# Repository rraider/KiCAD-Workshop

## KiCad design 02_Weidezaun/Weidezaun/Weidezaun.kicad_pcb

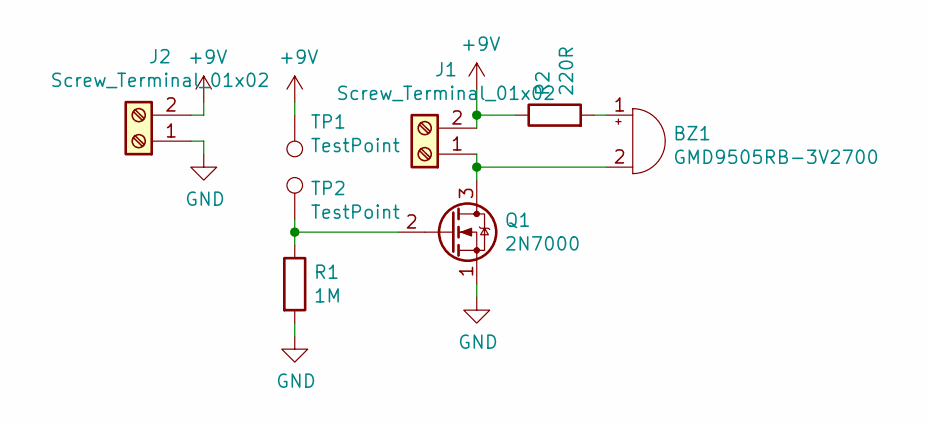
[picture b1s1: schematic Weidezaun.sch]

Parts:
BZ1: GMD9505RB-3V2700; Buzzer_TDK_PS1240P02BT_D12.2mm_H6.5mm
J1, J2: Screw_Terminal_01x02; TerminalBlock_bornier-2_P5.08mm
Q1: 2N7000; TO-92_Inline_Wide
R1: 1M; R_Axial_DIN0204_L3.6mm_D1.6mm_P7.62mm_Horizontal
R2: 220R; R_Axial_DIN0204_L3.6mm_D1.6mm_P7.62mm_Horizontal
TP1, TP2: TestPoint; testpoint_15x15

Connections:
+9V: J1.2, J2.2, R2.1, TP1.1
GND: J2.1, Q1.1 (S), R1.2
unnamed: BZ1.1 (-), R2.2
unnamed: BZ1.2 (+), J1.1, Q1.3 (D)
unnamed: Q1.2 (G), R1.1, TP2.1

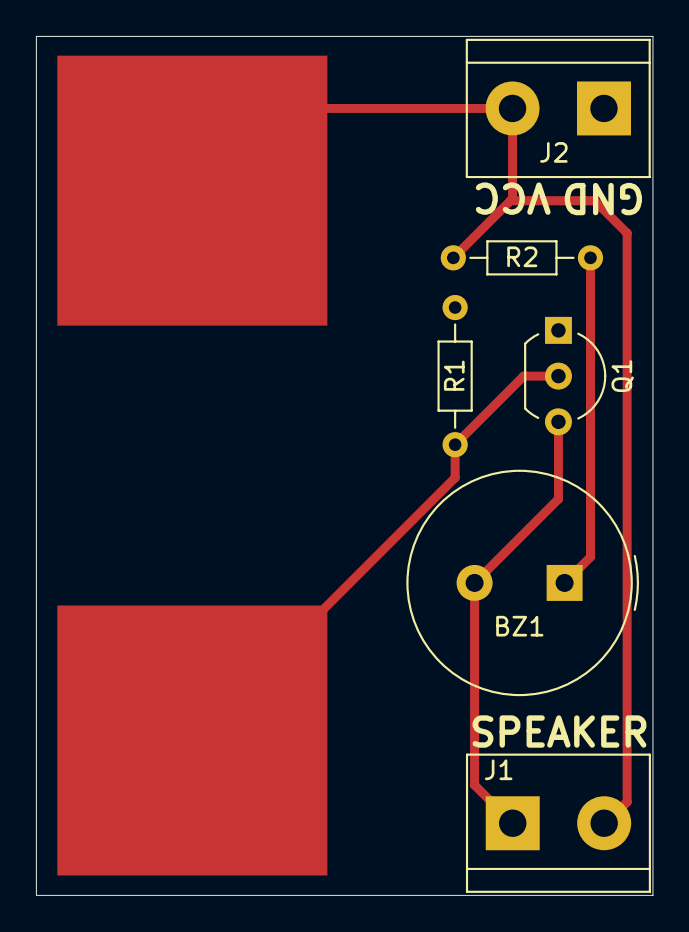
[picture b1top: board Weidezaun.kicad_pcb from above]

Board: 2 copper layers, 34.3 x 47.7 mm, 8 parts (0 on the bottom side), 5 nets.

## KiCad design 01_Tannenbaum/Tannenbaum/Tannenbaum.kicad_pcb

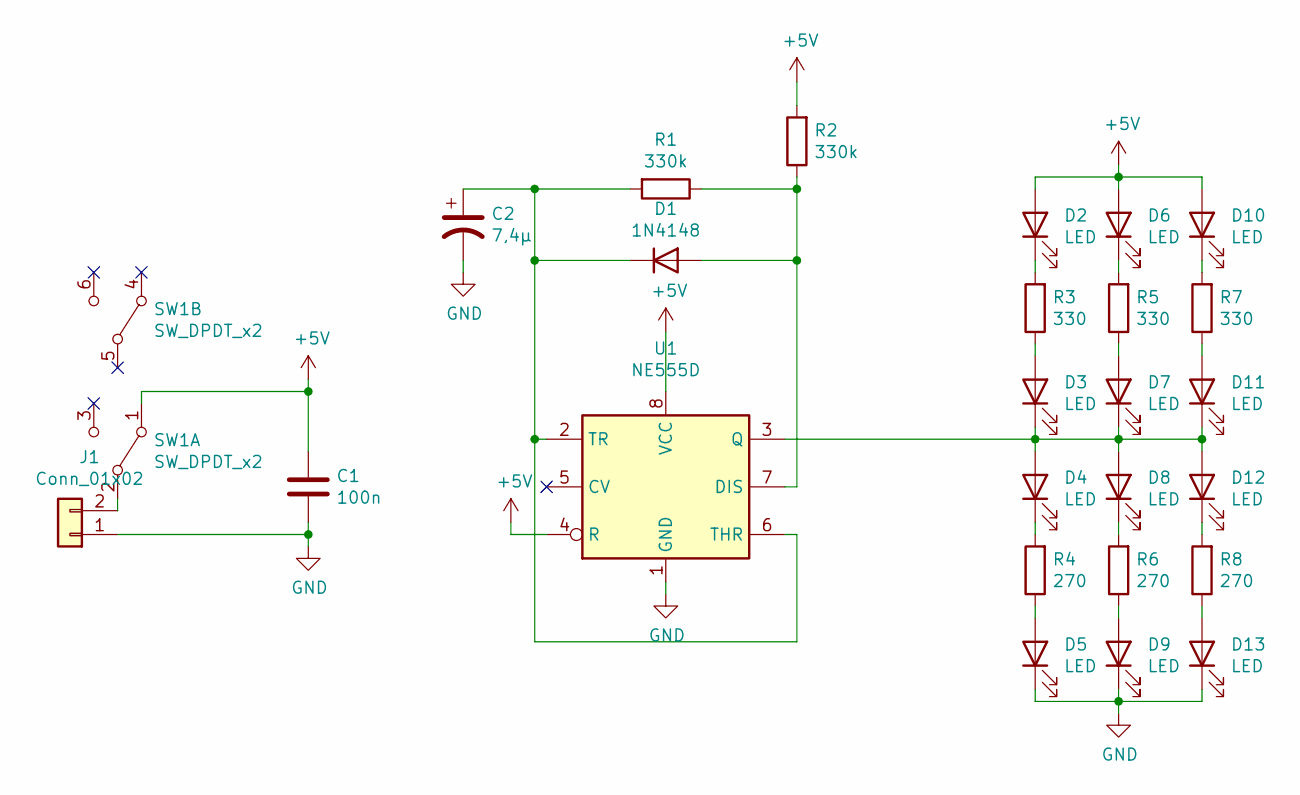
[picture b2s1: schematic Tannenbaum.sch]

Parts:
C1: 100n; C_Axial_L3.8mm_D2.6mm_P7.50mm_Horizontal
C2: 7,4µ; CP_Radial_D5.0mm_P2.00mm
D1: 1N4148; D_DO-35_SOD27_P7.62mm_Horizontal
D2, D3, D4, D5, D6, D7, D8, D9, D10, D11, D12, D13: LED; LED_D5.0mm
J1: Conn_01x02; TerminalBlock_bornier-2_P5.08mm
R1, R2: 330k; R_Axial_DIN0204_L3.6mm_D1.6mm_P7.62mm_Horizontal
R3, R5, R7: 330; R_Axial_DIN0204_L3.6mm_D1.6mm_P7.62mm_Horizontal
R4, R6, R8: 270; R_Axial_DIN0204_L3.6mm_D1.6mm_P7.62mm_Horizontal
SW1: SW_DPDT_x2; switch_dpdt
U1: NE555D; DIP-8_W7.62mm_LongPads

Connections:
+5V: C1.1, D2.2 (A), D6.2 (A), D10.2 (A), R2.2, SW1.1 (A), U1.4 (R), U1.8 (VCC)
GND: C1.2, C2.2, D5.1 (K), D9.1 (K), D13.1 (K), J1.1, U1.1 (GND)
unnamed: C2.1, D1.1 (K), R1.2, U1.2 (TR), U1.6 (THR)
unnamed: D1.2 (A), R1.1, R2.1, U1.7 (DIS)
unnamed: D2.1 (K), R3.2
unnamed: D3.2 (A), R3.1
unnamed: D4.1 (K), R4.2
unnamed: D5.2 (A), R4.1
unnamed: D6.1 (K), R5.2
unnamed: D7.2 (A), R5.1
unnamed: D8.1 (K), R6.2
unnamed: D9.2 (A), R6.1
unnamed: D10.1 (K), R7.2
unnamed: D3.1 (K), D4.2 (A), D7.1 (K), D8.2 (A), D11.1 (K), D12.2 (A), U1.3 (Q)
unnamed: D11.2 (A), R7.1
unnamed: D12.1 (K), R8.2
unnamed: D13.2 (A), R8.1
unnamed: J1.2, SW1.2 (B)

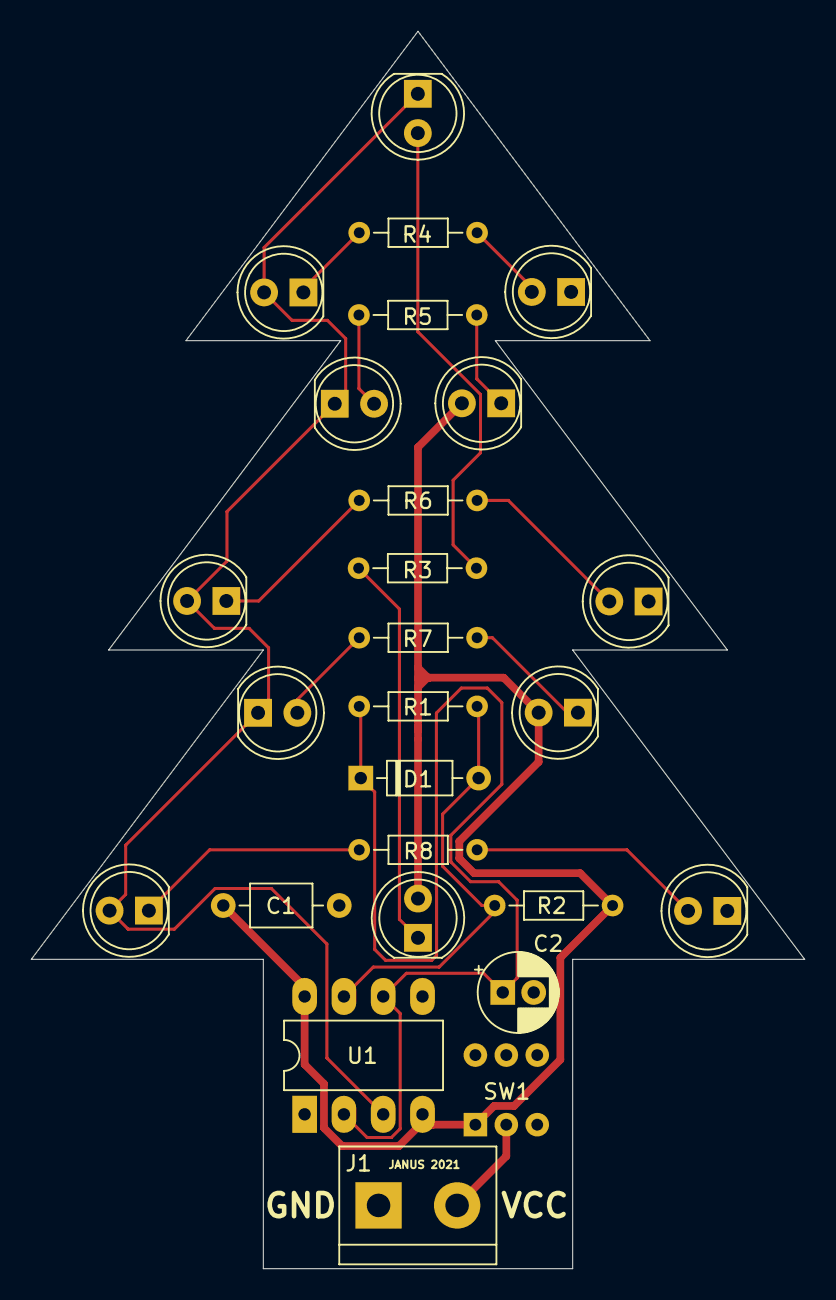
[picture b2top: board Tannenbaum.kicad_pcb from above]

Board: 2 copper layers, 50.0 x 80.0 mm, 26 parts (0 on the bottom side), 18 nets.

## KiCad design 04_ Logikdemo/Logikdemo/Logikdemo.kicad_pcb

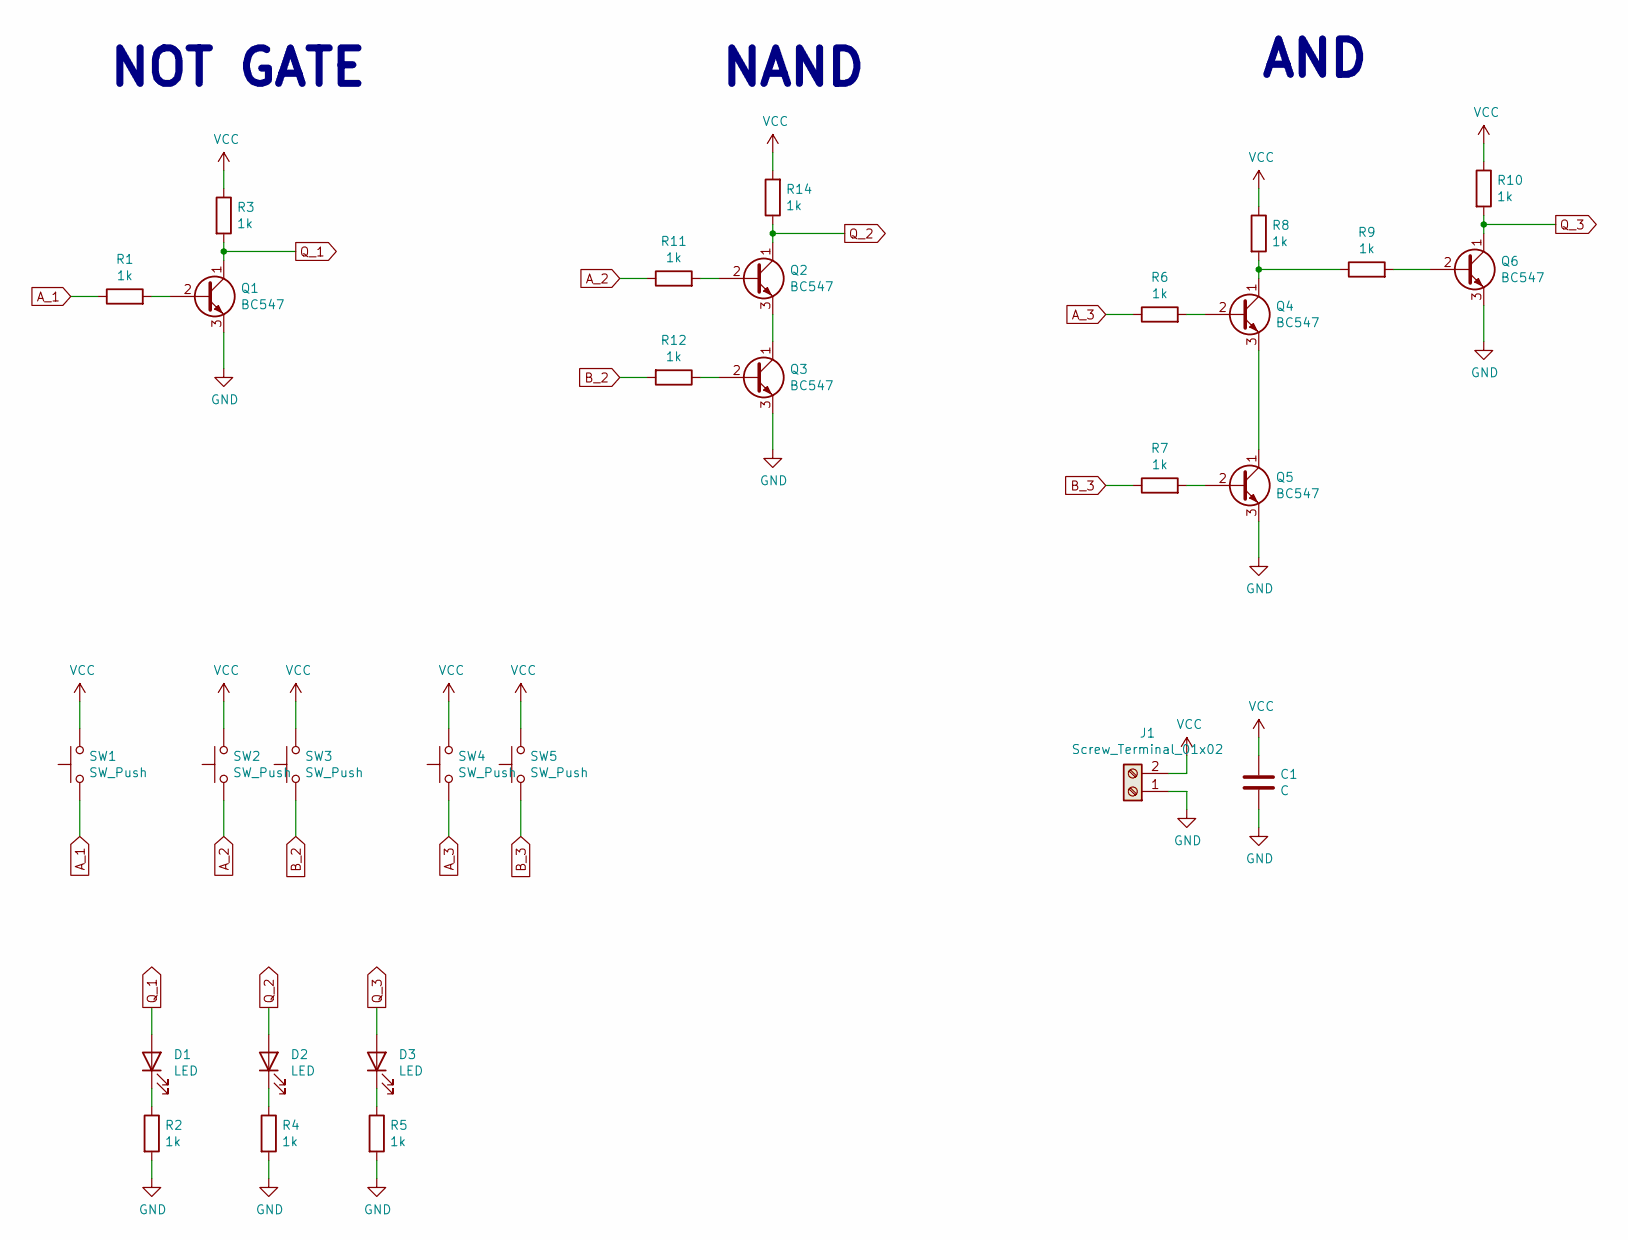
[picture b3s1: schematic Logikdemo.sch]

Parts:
C1: C; C_0805_2012Metric
D1, D2, D3: LED; LED_D5.0mm
J1: Screw_Terminal_01x02; TerminalBlock_bornier-2_P5.08mm
Q1, Q2, Q3, Q4, Q5, Q6: BC547; SOT-23
R1, R2, R3, R4, R5, R6, R7, R8, R9, R10, R11, R12, R14: 1k; R_0805_2012Metric
SW1, SW2, SW3, SW4, SW5: SW_Push; SW_PUSH_6mm

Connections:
A_1: R1.1, SW1.1
A_2: R11.1, SW2.1
A_3: R6.1, SW4.1
B_2: R12.2, SW3.1
B_3: R7.1, SW5.1
GND: C1.2, J1.1, Q1.3 (E), Q3.3 (E), Q5.3 (E), Q6.3 (E), R2.2, R4.2, R5.2
unnamed: D1.1 (K), R2.1
unnamed: D2.1 (K), R4.1
unnamed: D3.1 (K), R5.1
unnamed: Q1.2 (B), R1.2
unnamed: Q2.2 (B), R11.2
unnamed: Q2.3 (E), Q3.1 (C)
unnamed: Q3.2 (B), R12.1
unnamed: Q4.1 (C), R8.2, R9.1
unnamed: Q4.2 (B), R6.2
unnamed: Q4.3 (E), Q5.1 (C)
unnamed: Q5.2 (B), R7.2
unnamed: Q6.2 (B), R9.2
Q_1: D1.2 (A), Q1.1 (C), R3.2
Q_2: D2.2 (A), Q2.1 (C), R14.1
Q_3: D3.2 (A), Q6.1 (C), R10.2
VCC: C1.1, J1.2, R3.1, R8.1, R10.1, R14.2, SW1.2, SW2.2, SW3.2, SW4.2, SW5.2

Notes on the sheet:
NOT GATE
NAND
AND

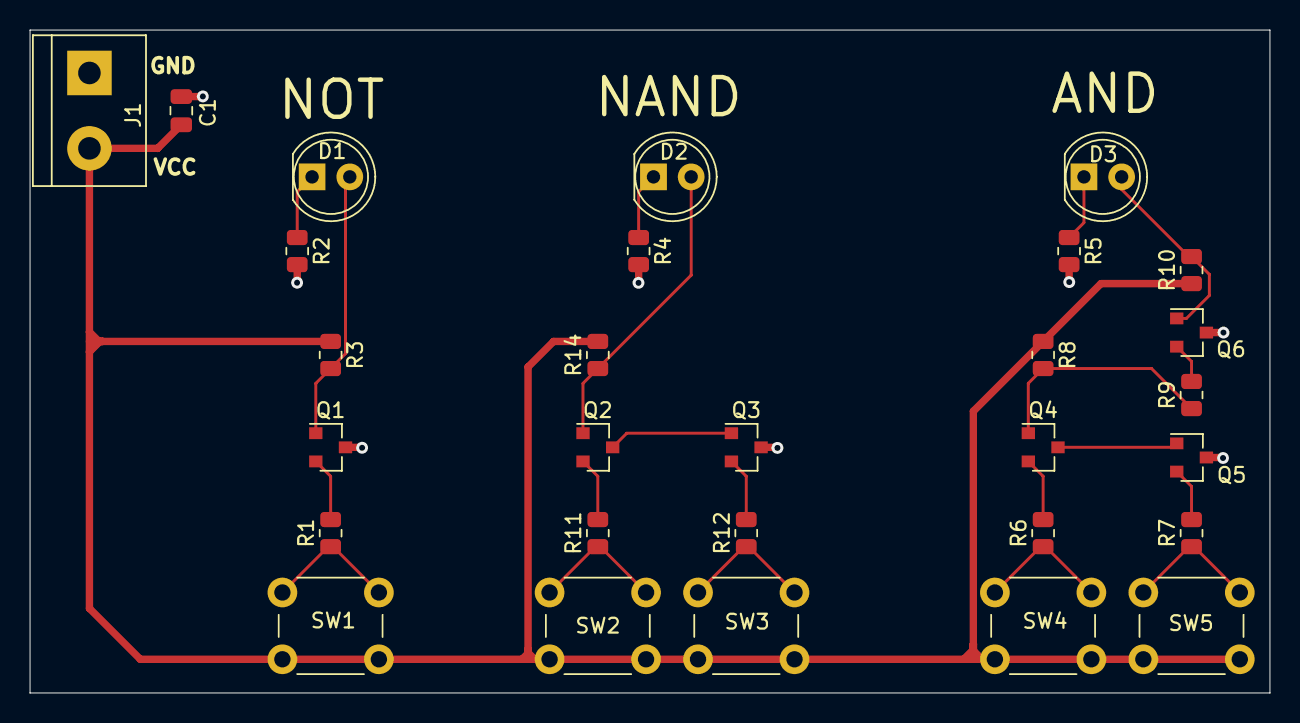
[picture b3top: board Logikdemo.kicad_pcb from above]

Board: 2 copper layers, 83.5 x 44.7 mm, 29 parts (0 on the bottom side), 22 nets.

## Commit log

2021-10-05 tansfer
2021-10-06 created schematic for 01
2021-10-06 review 01 schematic
2021-10-06 done 05 layout
2021-10-06 created pcb for 01; good night
2021-10-08 created 02
2021-10-09 recovered and routed 04
2021-10-09 relayouted 04
2021-10-10 review
2021-10-10 changed footprint
